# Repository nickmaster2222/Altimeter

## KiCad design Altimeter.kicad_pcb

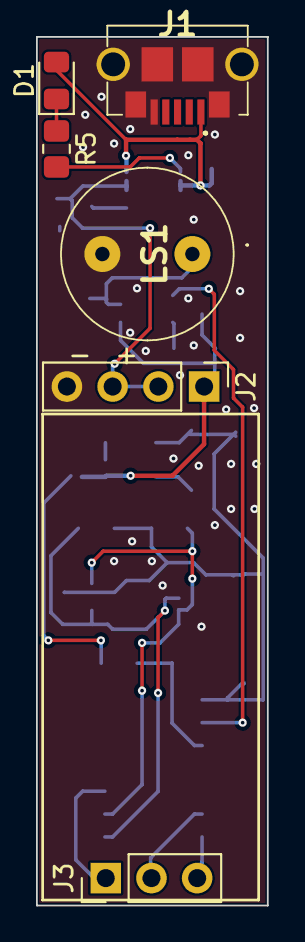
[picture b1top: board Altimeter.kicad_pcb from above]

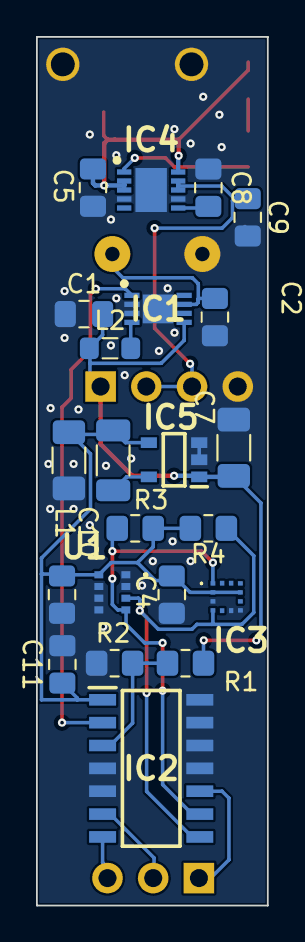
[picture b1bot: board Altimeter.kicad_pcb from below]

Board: 2 copper layers, 12.8 x 48.3 mm, 28 parts (22 on the bottom side), 17 nets.

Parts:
C1, C2: 10uF; C_0805_2012Metric_Pad1.18x1.45mm_HandSolder
C4, C6, C8, C11: .1uF; C_0805_2012Metric_Pad1.18x1.45mm_HandSolder
C5, C9: 5uF; C_0805_2012Metric_Pad1.18x1.45mm_HandSolder
C7, C10: 22uF; C_1206_3216Metric_Pad1.33x1.80mm_HandSolder
D1: LED; LED_0805_2012Metric_Pad1.15x1.40mm_HandSolder
IC1: DIO6605BFN8; SON50P300X200X80-9N-D
IC2: ATTINY804-SSF; SOIC127P600X175-14N
IC3: MC3479
IC4: MCP73855-I_MF; SON50P300X300X100-11N-D
IC5: XC9265B181MR-G; SOT95P280X130-5N
J1: USB3075-30-A; USB307530A
J2: Battery; PinHeader_1x04_P2.54mm_Vertical
J3: Conn_01x03_Female; PinHeader_1x03_P2.54mm_Vertical
L1: 10uH; L_1206_3216Metric_Pad1.22x1.90mm_HandSolder
L2: 4.7uF; L_0805_2012Metric_Pad1.05x1.20mm_HandSolder
LS1: CMI-9605-0580T; CMI96050580T
R1: 300K; R_0805_2012Metric_Pad1.20x1.40mm_HandSolder
R2: 100K; R_0805_2012Metric_Pad1.20x1.40mm_HandSolder
R3, R4: 4.7K; R_0805_2012Metric_Pad1.20x1.40mm_HandSolder
R5: 250; R_0805_2012Metric_Pad1.20x1.40mm_HandSolder
U1: ICP-10111; ICP10111

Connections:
/1.8V: C4.1, C6.1, C10.1, C11.1, IC2.1 (VDD), IC3.2 (CSN), IC3.9 (VDD), IC5.4 (VOUT), L1.2, R3.2, R4.2, U1.8 (VDD)
/5V: C5.1, D1.2 (A), IC4.2 (VSET), IC4.3 (VDD1), IC4.10 (EN), J1.1
/BAT: C1.2, C7.1, C9.1, IC1.5 (VIN), IC4.8 (VBAT1), IC4.9 (VBAT2), IC5.1 (VIN), J2.1, J2.2, J2.3, L2.1, R1.1
/BAT_DIV: IC2.3 (PA5), R1.2, R2.1
/BUZZER: IC1.1 (EN), IC2.2 (PA4)
/PROG: IC2.10 (PA0(~RESET/UPDI)), J3.1
/RX: IC2.6 (PB3), J3.2
/SCL: IC2.9 (PB0), IC3.1 (SCK_SCL), R3.1, U1.4 (SCL)
/SDA: IC2.8 (PB1), IC3.4 (DIN_SDA), R4.1, U1.3 (SDA)
/TX: IC2.7 (PB2), J3.3
Earth: C1.1, C2.2, C4.2, C5.2, C6.2, C7.2, C8.2, C9.2, C10.2, C11.2, IC1.2 (AGND), IC1.3 (PGND), IC1.9 (GND), IC2.4 (PA6), IC2.5 (PA7), IC2.11 (PA1), IC2.12 (PA2), IC2.13 (PA3(EXTCLK)), IC2.14 (GND), IC3.3 (DOUT_A6), IC3.6 (GND), IC3.7 (VPP), IC4.4 (VSS1), IC4.7 (VSS2), IC4.11 (EP), IC5.2 (GND), IC5.3 (CE), J1.5, J1.MH1, J1.MH2, J1.MP1, J1.MP2, J1.MP3, J1.MP4, J2.4, LS1.2 (-), R2.2, U1.1 (GND_1), U1.2 (RESV_1), U1.5 (RESV_2), U1.6 (RESV_3), U1.7 (GND_2)
unnamed: C2.1, IC1.7 (VOUT), LS1.1 (+)
unnamed: C8.1, IC4.6 (TIMER)
unnamed: D1.1 (K), R5.1
unnamed: IC1.4 (SW), L2.2
unnamed: IC4.1 (STAT1), R5.2
unnamed: IC5.5 (LX), L1.1

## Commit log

2022-03-27 done I think
2022-03-27 no done
2022-03-28 final?
2022-03-28 maybe actual final
2022-03-28 have to do
2022-03-28 change
